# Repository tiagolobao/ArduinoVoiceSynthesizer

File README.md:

# ArduinoVoiceSynthesizer
A Voice Synthesizer that uses, an Arduino, an amplifier and a SD Card

Um sintetizador de voz que utiliza um Arduino, um amplificador, e um cartão SD. Esse projeto veio de uma atividade de Pesquisa e Extensão que tem como objetivo gerar tecnologias assistivas de baixo custo.

Para explicações do código, leia o Wiki

-----------Pastas----------
  -> Code (Código)
  Essa pasta contém arquivos zip das bibliotecas usadas no projeto e a sketch arduino.
  -> Docs (Documentos)
  Contém todas os documentos envolvidos no projeto como listagem das sílabas e justificativas sociais
  -> PCI (Placa de circuito impresso)
  Contém todas os arquvios de squemático e board (Eagle). Próxima versão virá com Protoboard (Fritzing)
  -> Audio
  Contém todos os arquivos de audio .wav
  
---------Autores-----------
Grupo PET-Elétrica.
Líder: Tiago Lobão
Contibuições no código: Victor Hugo Magalhães, Vitor Invenção, Ryan Teixeira, Péricles Oliveira.
Contribuições do protótipo: Rafael Matos.

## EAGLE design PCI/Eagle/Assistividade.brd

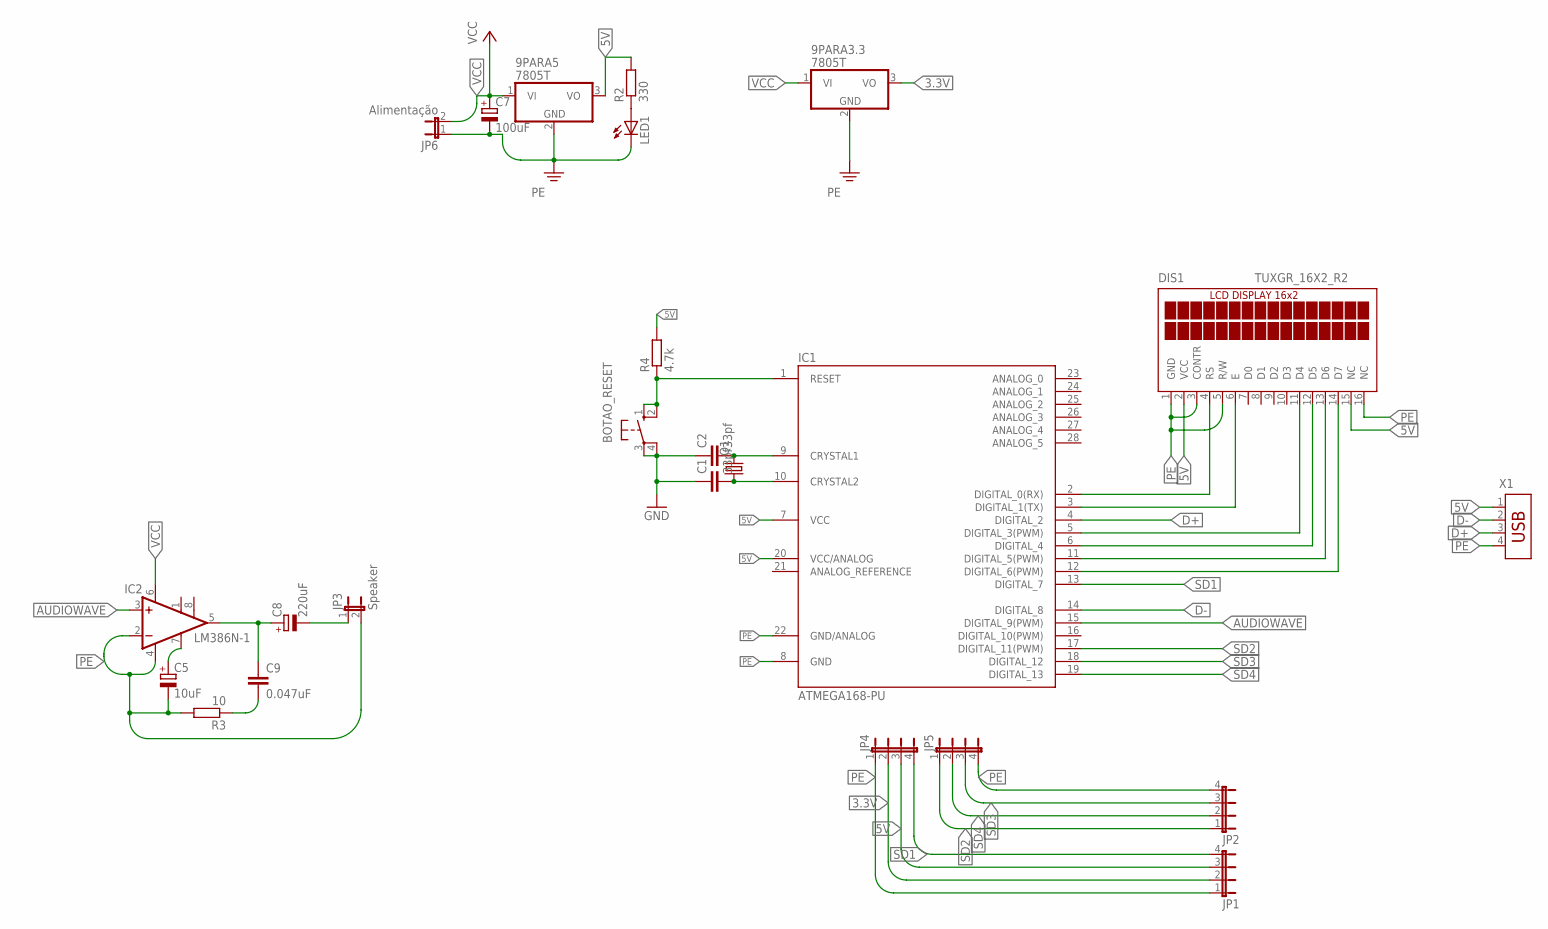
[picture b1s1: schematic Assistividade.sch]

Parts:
9PARA3.3, 9PARA5: 7805T; TO220H
BOTAO_RESET: 10-XX; B3F-10XX
C1, C2: 33pf; C025-024X044
C5: 10uF; E2,5-5
C7: 100uF; E2,5-6
C8: 220uF; E2,5-7
C9: 0.047uF; C050-025X075
DIS1: TUXGR_16X2_R2
IC1: ATMEGA168-PU; DIL28-3
IC2: LM386N-1; DIL08
JP1, JP2, JP4, JP5: JP4E; JP4
JP3: Speaker; JP1
JP6: Alimentação; JP1
LED1: LED5MM
Q1: CRYSTALHC49U-V; HC49U-V
R2: 330; 0207/10
R3: 10; 0207/10
R4: 4.7k; 0207/15
X1: USB-787616; USB

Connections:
3.3V: 9PARA3.3.3 (VO), JP1.2, JP4.2
5V: 9PARA5.3 (VO), DIS1.2 (VCC), DIS1.15 (NC), IC1.7 (VCC), IC1.20 (VCC/ANALOG), JP1.3, JP4.3, R2.2, R4.2, X1.1
AUDIOWAVE: IC1.15 (DIGITAL_9(PWM)), IC2.3 (+IN)
D+: IC1.4 (DIGITAL_2), X1.3
D-: IC1.14 (DIGITAL_8), X1.2
unnamed: C1.2, IC1.10 (CRYSTAL2), Q1.1
unnamed: C2.2, IC1.9 (CRYSTAL1), Q1.2
unnamed: BOTAO_RESET.1 (S), BOTAO_RESET.2 (S1), IC1.1 (RESET), R4.1
unnamed: C5.+, IC2.7 (BYPASS)
unnamed: LED1.A, R2.1
unnamed: DIS1.12 (D5), IC1.6 (DIGITAL_4)
unnamed: DIS1.13 (D6), IC1.11 (DIGITAL_5(PWM))
unnamed: DIS1.14 (D7), IC1.12 (DIGITAL_6(PWM))
unnamed: DIS1.4 (RS), IC1.2 (DIGITAL_0(RX))
unnamed: DIS1.6 (E), IC1.3 (DIGITAL_1(TX))
unnamed: DIS1.11 (D4), IC1.5 (DIGITAL_3(PWM))
unnamed: C9.2, R3.1
unnamed: C8.+, C9.1, IC2.5 (OUT)
unnamed: C8.-, JP3.1
PE: 9PARA3.3.2 (GND), 9PARA5.2 (GND), BOTAO_RESET.3, BOTAO_RESET.4 (P1), C1.1, C2.1, C5.-, C7.-, DIS1.1 (GND), DIS1.3 (CONTR), DIS1.5 (R/W), DIS1.16 (NC), IC1.8 (GND), IC1.22 (GND/ANALOG), IC2.2 (-IN), IC2.4 (GND), JP1.1, JP2.4, JP3.2, JP4.1, JP5.4, JP6.1, LED1.K (C), R3.2, X1.4
SD1: IC1.13 (DIGITAL_7), JP1.4, JP4.4
SD2: IC1.17 (DIGITAL_11(PWM)), JP2.1, JP5.1
SD3: IC1.18 (DIGITAL_12), JP2.3, JP5.3
SD4: IC1.19 (DIGITAL_13), JP2.2, JP5.2
VCC: 9PARA3.3.1 (VI), 9PARA5.1 (VI), C7.+, IC2.6 (VS), JP6.2

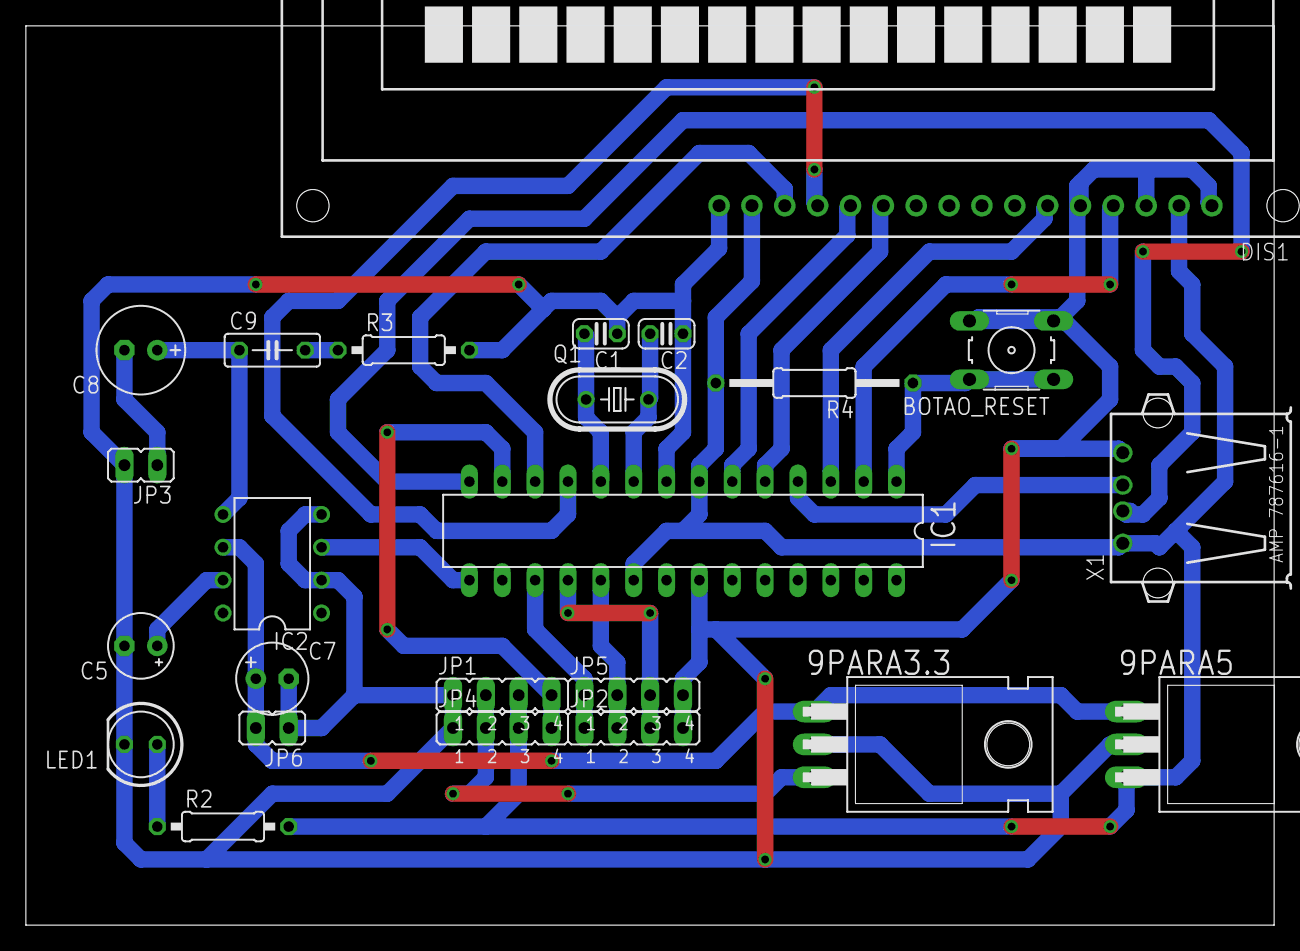
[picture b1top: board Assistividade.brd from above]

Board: 2 copper layers, 96.5 x 69.5 mm, 24 parts (0 on the bottom side), 25 nets.

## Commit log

2015-10-11 + Informações
    Existe outro readme para explicação de como funciona a o código na pasta Code
2015-10-12 Arduino Firmware Upload
2015-10-12 Add arquivos
2015-10-12 Update
    Coloque a verdadeira ultima versão e fiz alguns comentários
2015-10-12 Bibliotecas
    Bibliotecas externas usadas
2016-02-23 Added files via upload
2016-02-23 Create s
2016-02-23 Create t
2016-02-23 Create u
2016-02-23 Create v
2016-02-23 Create z
